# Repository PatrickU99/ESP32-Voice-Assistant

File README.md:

# ESP32-S3 Voice Assistant

A voice assistant built on the ESP32-S3 that records audio, 
transcribes it using Deepgram, sends it to Groq AI for a response, 
and plays it back through a speaker.

## Hardware
- ESP32-S3 N16R8
- INMP441 Microphone
- MAX98357A Amplifier
- SSD1306 OLED Display
- PIR Motion Sensor

## Features
- Speech to text via Deepgram
- AI responses via Groq
- Text to speech playback
- OLED display output

## Setup
1. Copy `include/config_template.h` to `include/config.h`
2. Fill in your WiFi and API credentials
3. Upload via PlatformIO

# Important details
main code:
VoiceAssistant -> src -> main.cpp

Schematic:
VoiceAssistantHW -> VoiceAssistantHW-backups -> VoiceAssistantHW/VoiceAssistantHW-backups/VoiceAssistantHW-2026-06-05_164113.zip

# Demo
video demo link:https://github.com/PatrickU99/ESP32-Voice-Assistant/releases/download/v1.0.0/IMG_6454.MOV

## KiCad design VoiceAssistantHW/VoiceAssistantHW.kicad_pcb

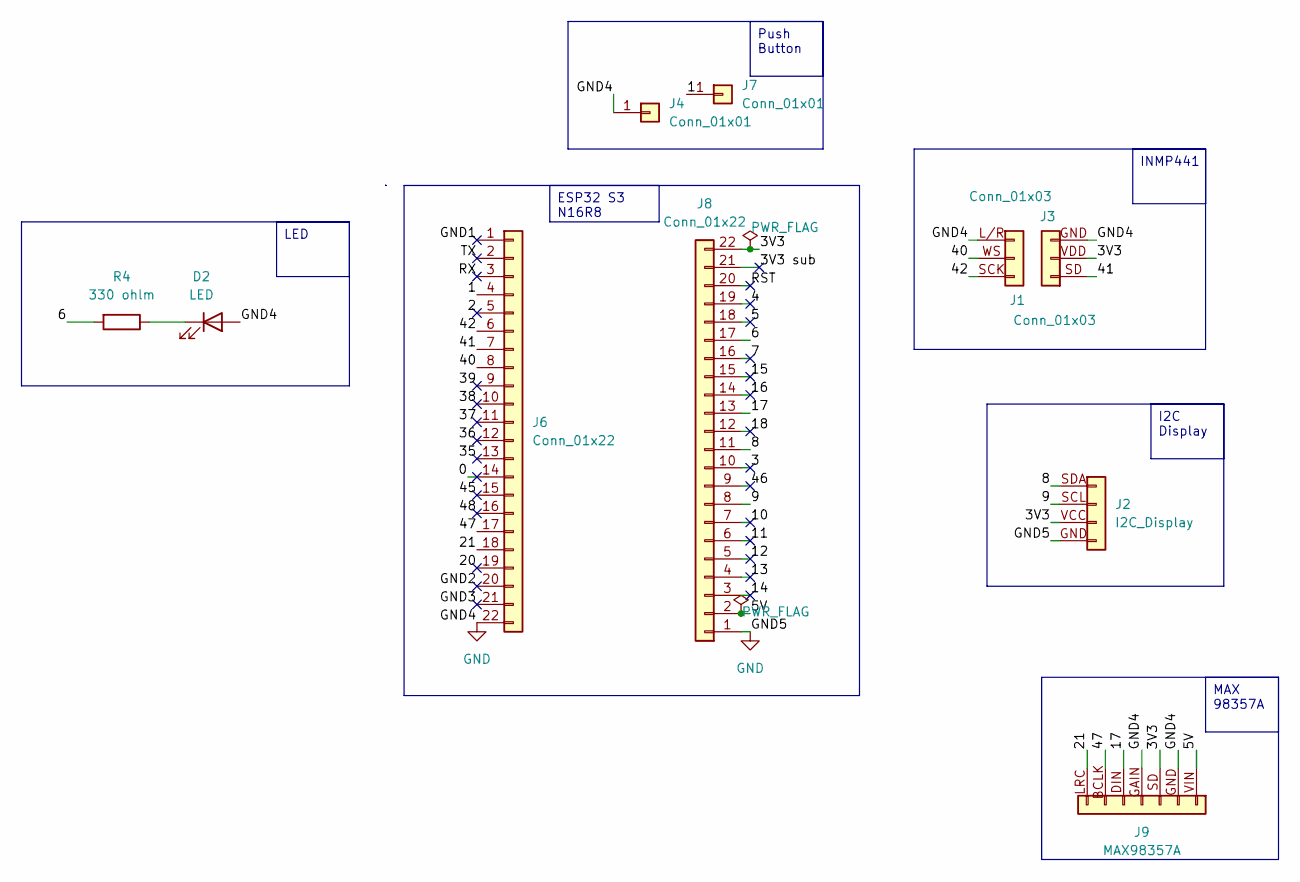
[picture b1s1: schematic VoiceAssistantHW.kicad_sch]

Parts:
D2: LED; LED_0201_0603Metric
J1, J3: Conn_01x03; Molex_SL_171971-0003_1x03_P2.54mm_Vertical
J2: I2C_Display; Molex_SL_171971-0004_1x04_P2.54mm_Vertical
J4, J7: Conn_01x01; PinSocket_1x01_P2.54mm_Vertical
J6, J8: Conn_01x22; Molex_SL_171971-0022_1x22_P2.54mm_Vertical
J9: MAX98357A; Molex_SL_171971-0007_1x07_P2.54mm_Vertical
R4: 330 ohlm; R_0201_0603Metric

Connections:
/0: J6.14
/1: J6.4, J7.1
/2: J6.5
/3: J8.10
/3V3: J2.VCC (Pin_3), J3.VDD (Pin_2), J8.22, J9.SD (Pin_3)
/3V3 sub: J8.21
/4: J8.19
/5: J8.18
/5V: J8.2, J9.VIN (Pin_1)
/6: J8.17, R4.2
/7: J8.16
/8: J2.SDA (Pin_1), J8.11
/9: J2.SCL (Pin_2), J8.8
/10: J8.7
/11: J8.6
/12: J8.5
/13: J8.4
/14: J8.3
/15: J8.15
/16: J8.14
/17: J8.13, J9.DIN (Pin_5)
/18: J8.12
/20: J6.19
/21: J6.18, J9.LRC (Pin_7)
/35: J6.13
/36: J6.12
/37: J6.11
/38: J6.10
/39: J6.9
/40: J1.WS (Pin_2), J6.8
/41: J3.SD (Pin_1), J6.7
/42: J1.SCK (Pin_3), J6.6
/45: J6.15
/46: J8.9
/47: J6.17, J9.BCLK (Pin_6)
/48: J6.16
/GND1: J6.1
/GND2: J6.20
/GND3: J6.21
/RST: J8.20
/RX: J6.3
/TX: J6.2
GND: D2.2 (A), J1.L/R (Pin_1), J2.GND (Pin_4), J3.GND (Pin_3), J4.1, J6.22, J8.1, J9.GAIN (Pin_4), J9.GND (Pin_2)
unnamed: D2.1 (K), R4.1

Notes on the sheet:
LED
ESP32 S3 N16R8
I2C Display
MAX 98357A
INMP441
Push Button

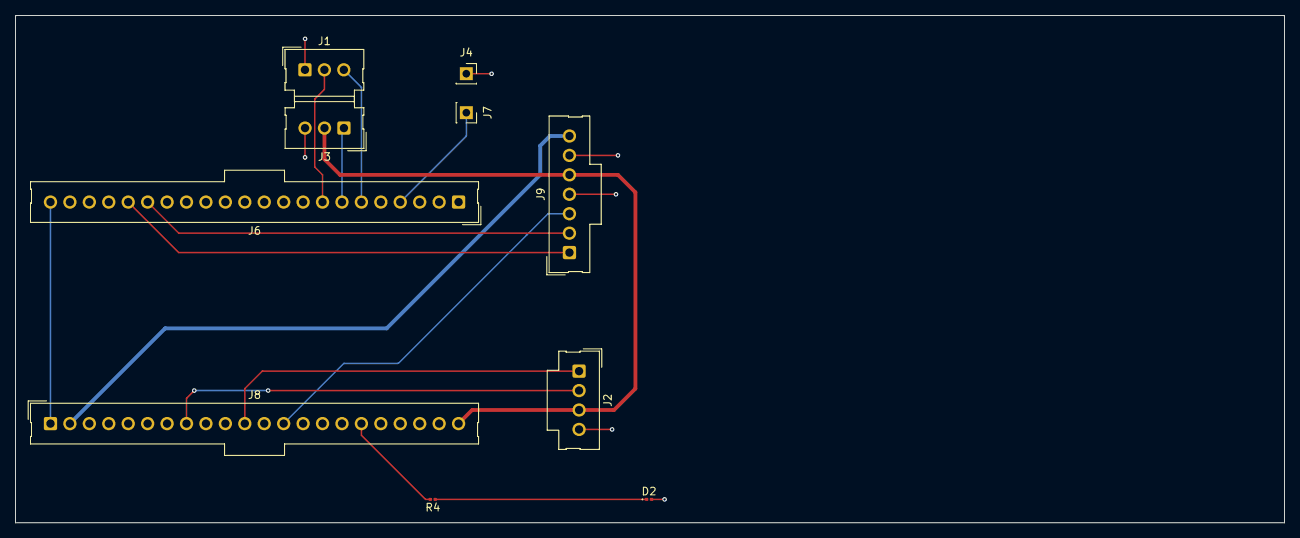
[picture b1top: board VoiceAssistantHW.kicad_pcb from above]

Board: 2 copper layers, 165.9 x 66.3 mm, 10 parts (0 on the bottom side), 14 nets.

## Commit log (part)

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2026-06-05 Remove config.h from tracking
2026-06-05 Remove sensitive files
2026-06-05 Add KiCad schematic and PCB layout
2026-06-05 Add README
2026-06-06 Update README.md
    added the video
